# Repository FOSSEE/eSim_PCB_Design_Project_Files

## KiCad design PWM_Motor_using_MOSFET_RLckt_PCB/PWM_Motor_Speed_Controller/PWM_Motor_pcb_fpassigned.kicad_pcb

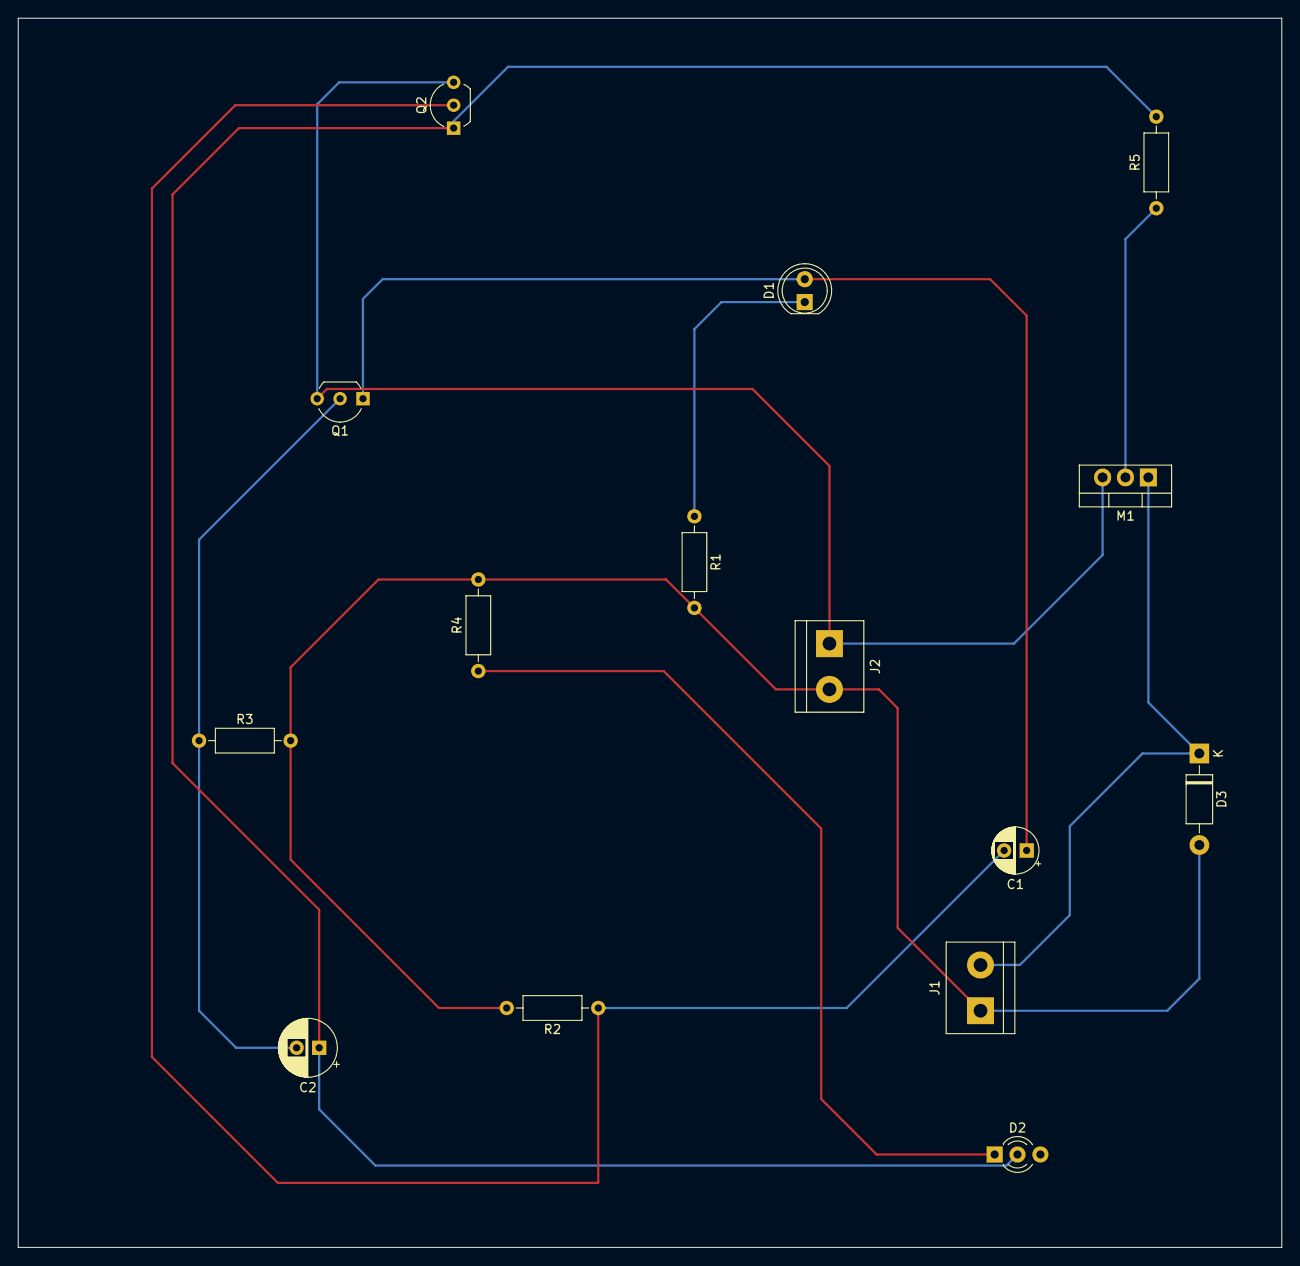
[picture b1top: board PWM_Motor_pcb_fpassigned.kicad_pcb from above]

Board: 2 copper layers, 140.2 x 136.4 mm, 15 parts (0 on the bottom side), 10 nets.

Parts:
C1: 100n; CP_Radial_D5.0mm_P2.50mm
C2: 100n; CP_Radial_D6.3mm_P2.50mm
D1: eSim_LED; LED_D5.0mm
D2: eSim_LED; LED_D3.0mm-3
D3: eSim_Diode; D_DO-41_SOD81_P10.16mm_Horizontal
J1, J2: eSim_2PinConn; TerminalBlock_bornier-2_P5.08mm
M1: eSim_MOS_N; TO-220-3_Vertical
Q1, Q2: eSim_NPN; TO-92_Inline_Wide
R1, R4: 1K; R_Axial_DIN0207_L6.3mm_D2.5mm_P10.16mm_Horizontal
R2: 33k; R_Axial_DIN0207_L6.3mm_D2.5mm_P10.16mm_Horizontal
R3: 100k; R_Axial_DIN0207_L6.3mm_D2.5mm_P10.16mm_Horizontal
R5: 100; R_Axial_DIN0207_L6.3mm_D2.5mm_P10.16mm_Horizontal

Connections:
GND: J2.1, M1.3 (S), Q1.3 (E), Q2.3 (E)
unnamed: C1.1, D1.2 (K), Q1.1 (C)
unnamed: C1.2, Q2.2 (B), R2.1
unnamed: C2.1, D2.2 (K), Q2.1 (C), R5.2
unnamed: C2.2, Q1.2 (B), R3.1
unnamed: D1.1 (A), R1.1
unnamed: D2.1 (A), R4.1
unnamed: D3.1 (A), J1.2, M1.1 (D)
unnamed: D3.2 (K), J1.1, J2.2, R1.2, R2.2, R3.2, R4.2
unnamed: M1.2 (G), R5.1

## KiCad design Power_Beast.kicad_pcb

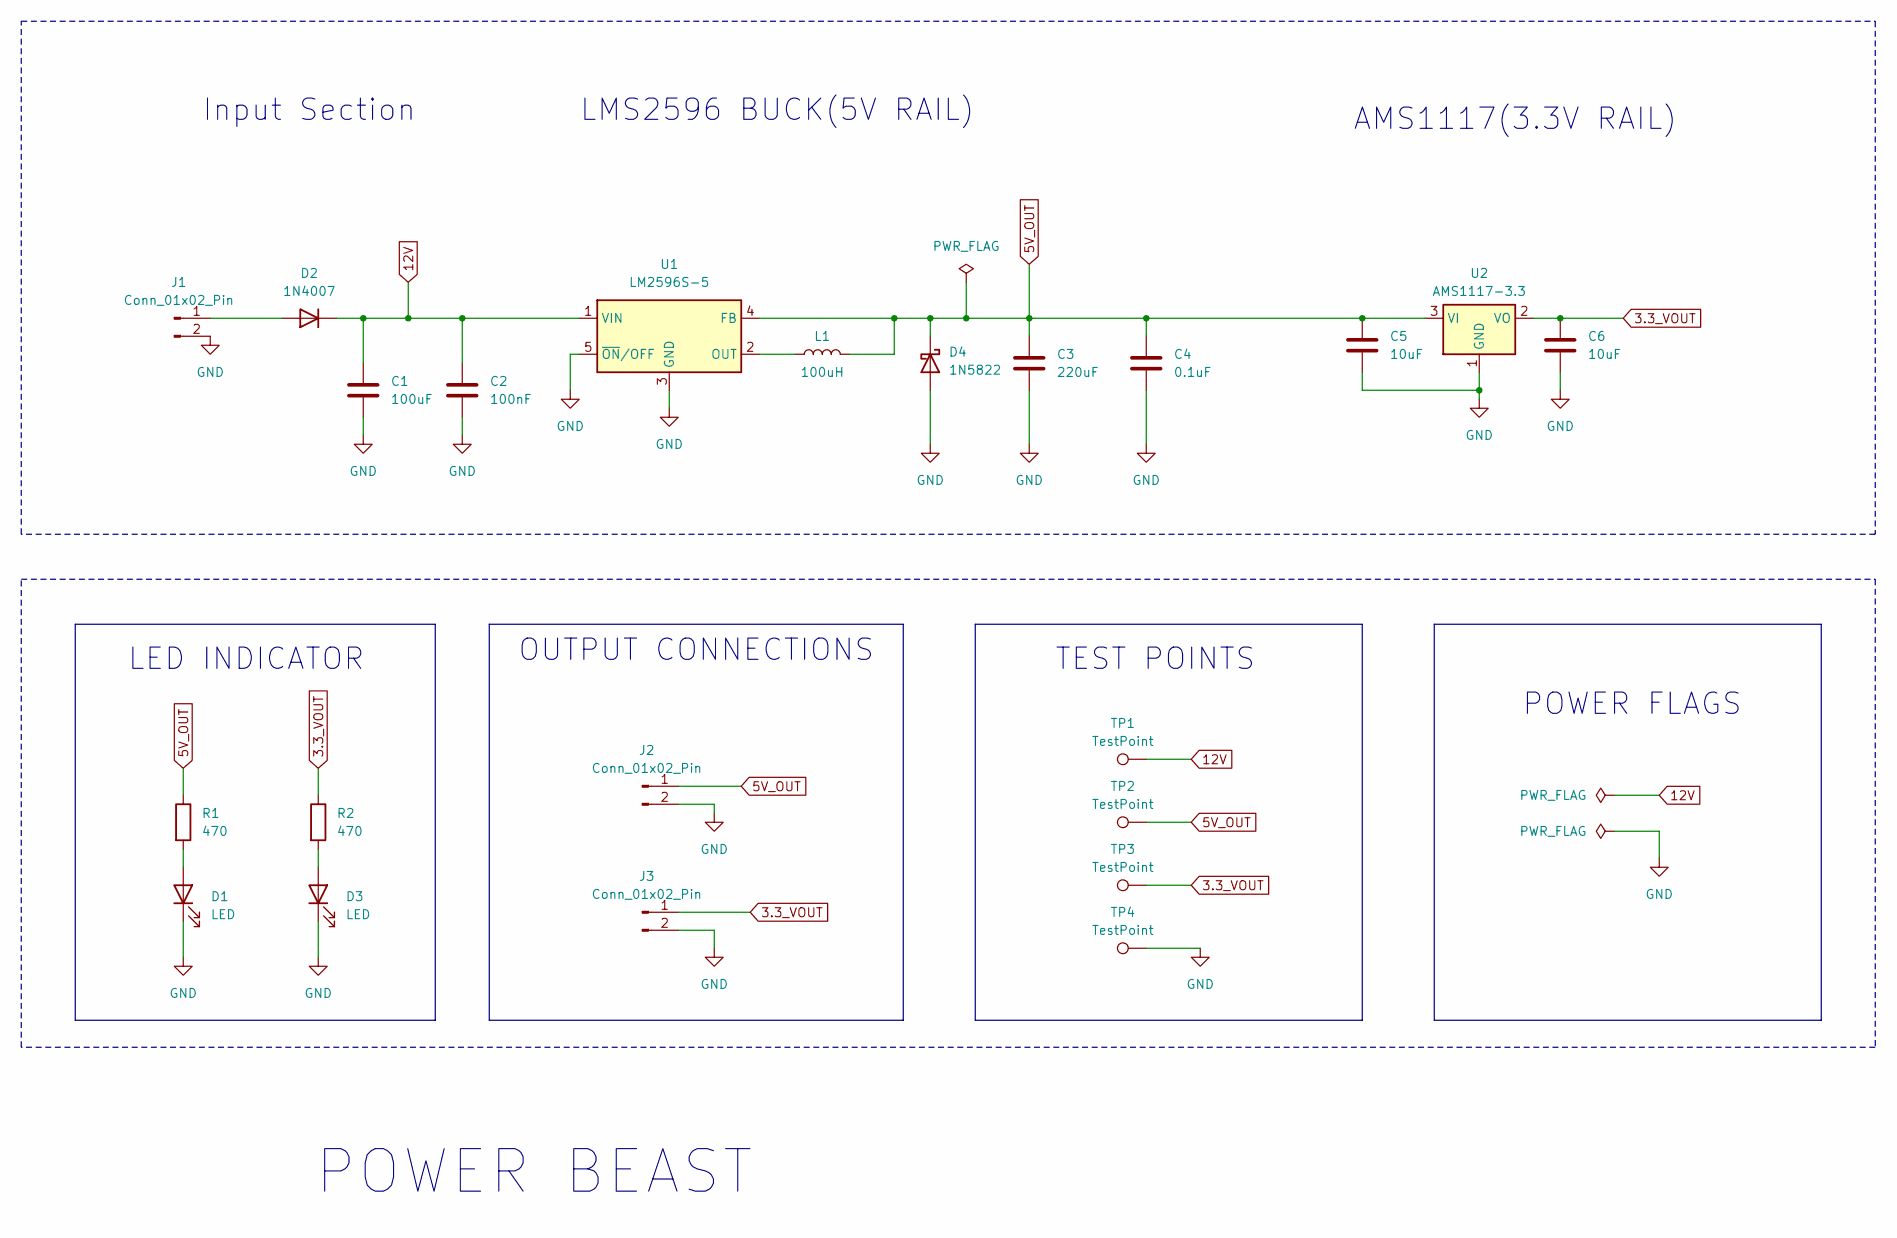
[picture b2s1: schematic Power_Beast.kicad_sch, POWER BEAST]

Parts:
C1: 100uF; CP_Radial_D8.0mm_P3.50mm
C2: 100nF; C_0805_2012Metric
C3: 220uF; CP_Radial_D8.0mm_P3.50mm
C4: 0.1uF; C_0805_2012Metric
C5, C6: 10uF; C_0805_2012Metric
D1, D3: LED; LED_D3.0mm
D2: 1N4007; D_DO-41_SOD81_P10.16mm_Horizontal
D4: 1N5822; D_DO-27_P12.70mm_Horizontal
J1, J2, J3: Conn_01x02_Pin; PinHeader_1x02_P2.54mm_Vertical
L1: 100uH; L_Axial_L9.5mm_D4.0mm_P15.24mm_Horizontal_Fastron_SMCC
R1, R2: 470; R_0805_2012Metric
TP1, TP2, TP3, TP4: TestPoint; TestPoint_Pad_D2.0mm
U1: LM2596S-5; TO-263-5_TabPin6
U2: AMS1117-3.3; SOT-223-3_TabPin2

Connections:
3.3_VOUT: C6.2, J3.1, R2.1, TP3.1 (1_1), U2.2 (VO)
5V_OUT: C3.1, C4.1, C5.1, D4.1 (K), J2.1, L1.2, R1.1, TP2.1 (1_1), U1.4 (FB), U2.3 (VI)
12V: C1.1, C2.1, D2.1 (K), TP1.1 (1_1), U1.1 (VIN)
GND: C1.2, C2.2, C3.2, C4.2, C5.2, C6.1, D1.1 (K), D3.1 (K), D4.2 (A), J1.2, J2.2, J3.2, TP4.1 (1_1), U1.3 (GND), U1.5 (~ON/OFF), U2.1 (GND)
unnamed: D1.2 (A), R1.2
unnamed: D2.2 (A), J1.1
unnamed: D3.2 (A), R2.2
unnamed: L1.1, U1.2 (OUT)

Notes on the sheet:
POWER BEAST
Input Section
LMS2596 BUCK(5V RAIL)
OUTPUT CONNECTIONS
POWER FLAGS
TEST POINTS
LED INDICATOR
AMS1117(3.3V RAIL)

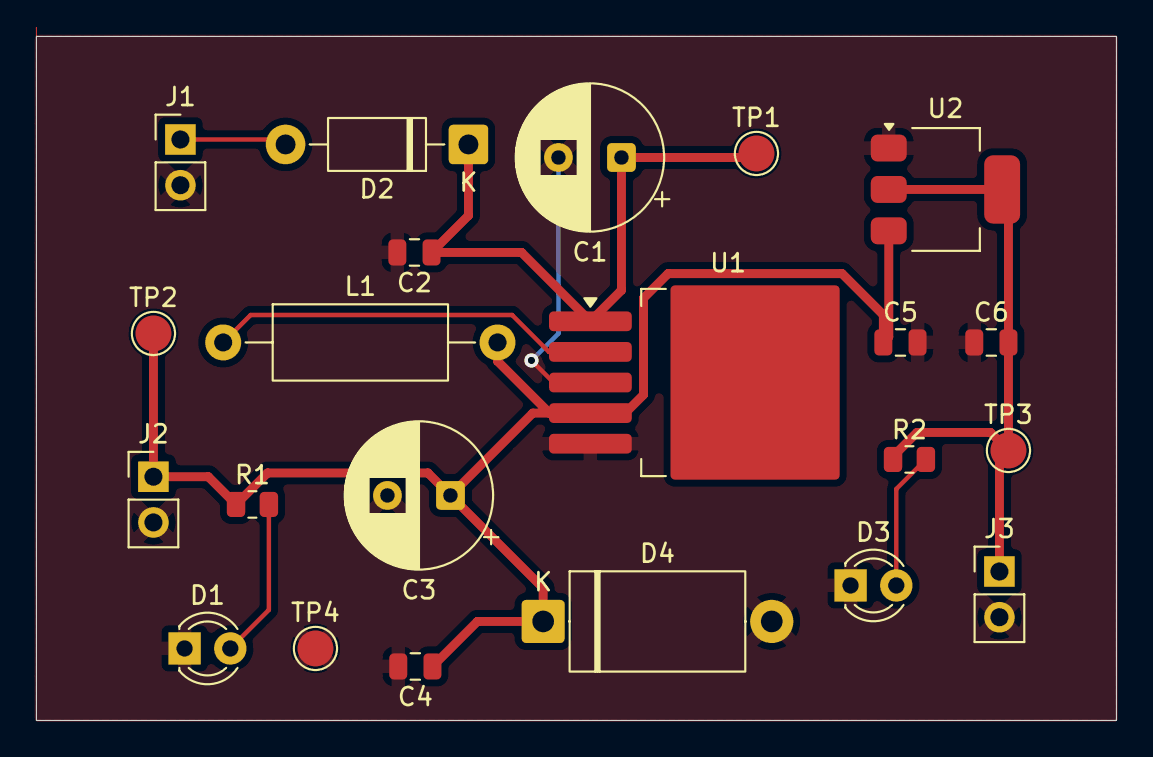
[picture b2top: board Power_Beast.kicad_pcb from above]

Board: 2 copper layers, 60.0 x 38.0 mm, 22 parts (0 on the bottom side), 8 nets.

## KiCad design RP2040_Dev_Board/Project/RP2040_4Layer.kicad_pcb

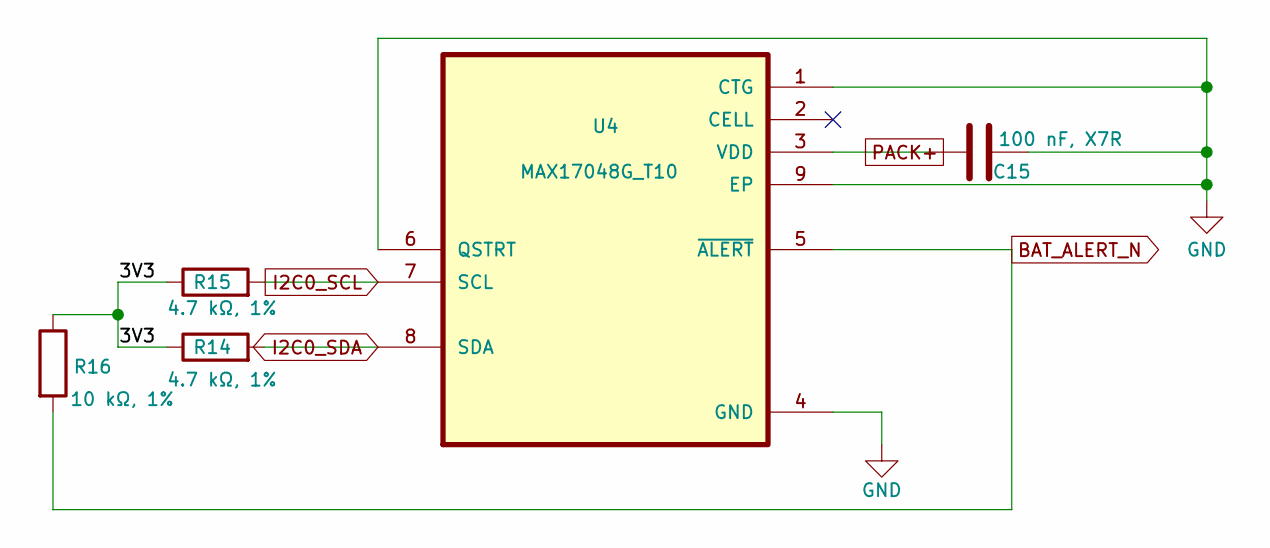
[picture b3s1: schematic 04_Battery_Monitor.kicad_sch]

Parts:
C15: 100 nF, X7R; C_0603_1608Metric
R14, R15: 4.7 kΩ, 1%; R_0603_1608Metric
R16: 10 kΩ, 1%; R_0603_1608Metric
U4: MAX17048G_T10; MAX17048G_T10SON50P200X200X80-9N; MPN MAX17048G+T10

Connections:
/04_Battery_Monitor/3V3: R14.1, R15.1, R16.1
BAT_ALERT_N: R16.2, U4.5 (~ALERT); also elsewhere on the board
GND: C15.2, U4.1 (CTG), U4.4 (GND), U4.6 (QSTRT), U4.9 (EP); also elsewhere on the board
I2C0_SCL: R15.2, U4.7 (SCL); also elsewhere on the board
I2C0_SDA: R14.2, U4.8 (SDA); also elsewhere on the board
PACK+: C15.1, U4.3 (VDD); also elsewhere on the board

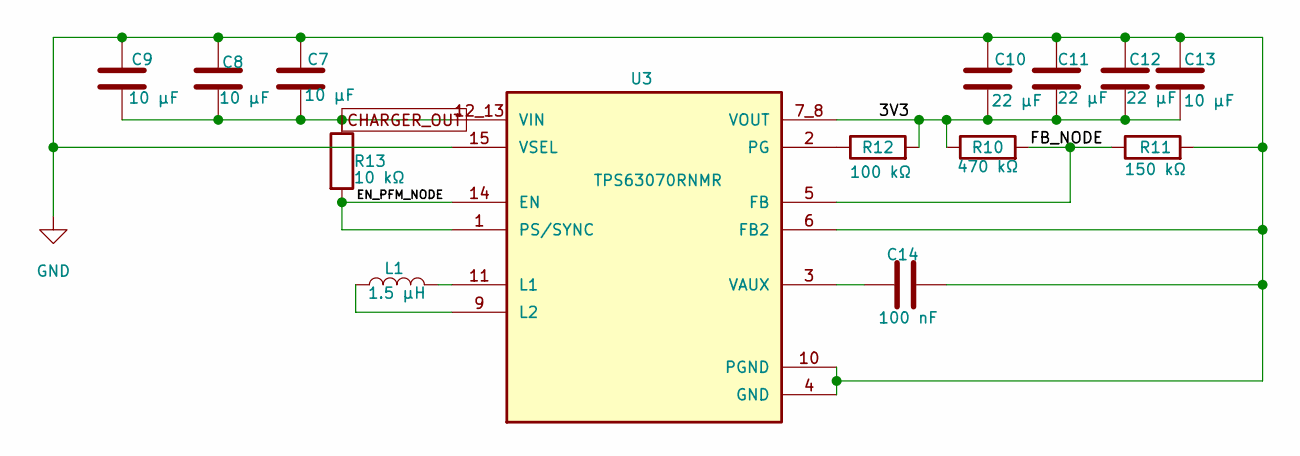
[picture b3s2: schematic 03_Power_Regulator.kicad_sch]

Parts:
C7, C8, C9, C13: 10 µF; C_0805_2012Metric
C10, C11, C12: 22 µF; C_1206_3216Metric
C14: 100 nF; C_0603_1608Metric
L1: 1.5 µH; L_Coilcraft_XxL4020
R10: 470 kΩ; R_0603_1608Metric
R11: 150 kΩ; R_0603_1608Metric
R12: 100 kΩ; R_0603_1608Metric
R13: 10 kΩ; R_0603_1608Metric
U3: TPS63070RNMR; VREG_TPS63070RNMR; MPN TPS63070RNMR

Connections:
/03_Power_Regulator/3V3: C10.2, C11.2, C12.2, C13.2, R10.1, R12.2, U3.7_8 (VOUT)
/03_Power_Regulator/EN_PFM_NODE: R13.2, U3.1 (PS/SYNC), U3.14 (EN)
/03_Power_Regulator/FB_NODE: R10.2, R11.1, U3.5 (FB)
CHARGER_OUT: C7.2, C8.2, C9.2, R13.1, U3.12_13 (VIN); also elsewhere on the board
GND: C7.1, C8.1, C9.1, C10.1, C11.1, C12.1, C13.1, C14.2, R11.2, U3.4 (GND), U3.6 (FB2), U3.10 (PGND), U3.15 (VSEL); also elsewhere on the board
unnamed: L1.2, U3.11 (L1)
unnamed: L1.1, U3.9 (L2)
unnamed: R12.1, U3.2 (PG)
unnamed: C14.1, U3.3 (VAUX)

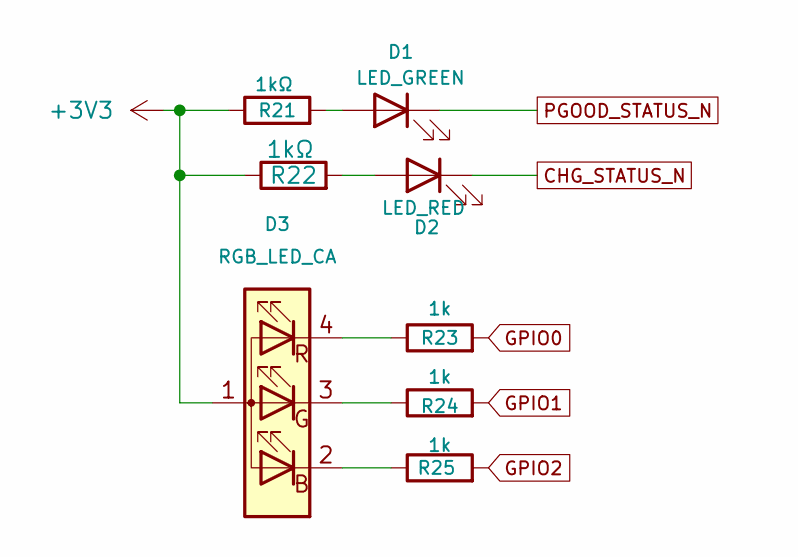
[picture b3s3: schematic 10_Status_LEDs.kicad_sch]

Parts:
D1: LED_GREEN; LED_0603_1608Metric
D2: LED_RED; LED_0603_1608Metric
D3: RGB_LED_CA; LED_Avago_PLCC4_3.2x2.8mm_CW
R21, R22: 1kΩ; R_0603_1608Metric
R23, R24, R25: 1k; R_0603_1608Metric

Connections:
+3V3: D3.1 (A), R21.1, R22.1; also elsewhere on the board
CHG_STATUS_N: D2.1 (K); also elsewhere on the board
GPIO0: R23.2; also elsewhere on the board
GPIO1: R24.2; also elsewhere on the board
GPIO2: R25.2; also elsewhere on the board
unnamed: D1.2 (A), R21.2
unnamed: D2.2 (A), R22.2
unnamed 51: D3.2 (BK), R25.1; also elsewhere on the board
unnamed 52: D3.3 (GK), R24.1; also elsewhere on the board
unnamed 53: D3.4 (RK), R23.1; also elsewhere on the board
PGOOD_STATUS_N: D1.1 (K); also elsewhere on the board

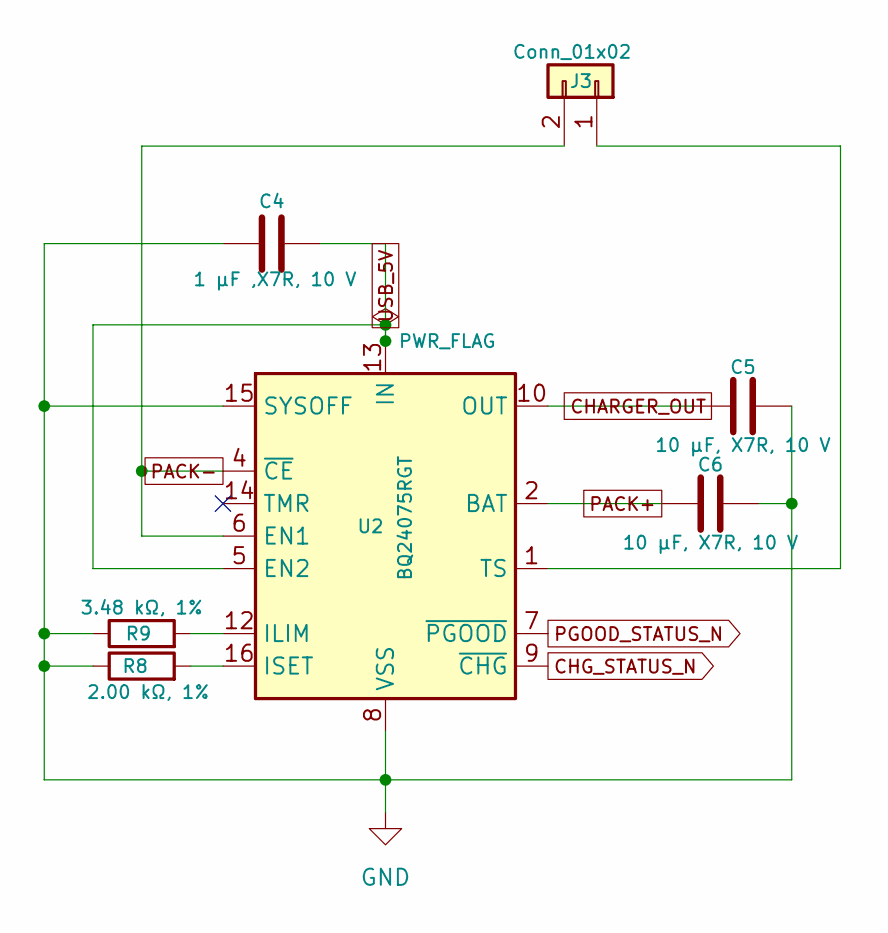
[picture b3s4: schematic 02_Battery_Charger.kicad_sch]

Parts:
C4: 1 µF ,X7R, 10 V; C_0603_1608Metric
C5, C6: 10 µF, X7R, 10 V; C_0805_2012Metric
J3: Conn_01x02; JST_PH_S2B-PH-K_1x02_P2.00mm_Horizontal
R8: 2.00 kΩ, 1%; R_0603_1608Metric
R9: 3.48 kΩ, 1%; R_0603_1608Metric
U2: BQ24075RGT; VQFN-16-1EP_3x3mm_P0.5mm_EP1.6x1.6mm

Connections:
CHARGER_OUT: C5.1, U2.10 (OUT), U2.11 (OUT); also elsewhere on the board
CHG_STATUS_N: U2.9 (~CHG); also elsewhere on the board
GND: C4.1, C5.2, C6.2, R8.1, R9.1, U2.8 (VSS), U2.15 (SYSOFF), U2.17 (VSS); also elsewhere on the board
unnamed 57: J3.1, U2.1 (TS); also elsewhere on the board
unnamed: R9.2, U2.12 (ILIM)
unnamed: R8.2, U2.16 (ISET)
PACK+: C6.1, U2.2 (BAT), U2.3 (BAT); also elsewhere on the board
PACK-: J3.2, U2.4 (~CE), U2.6 (EN1); also elsewhere on the board
PGOOD_STATUS_N: U2.7 (~PGOOD); also elsewhere on the board
USB_5V: C4.2, U2.5 (EN2), U2.13 (IN); also elsewhere on the board

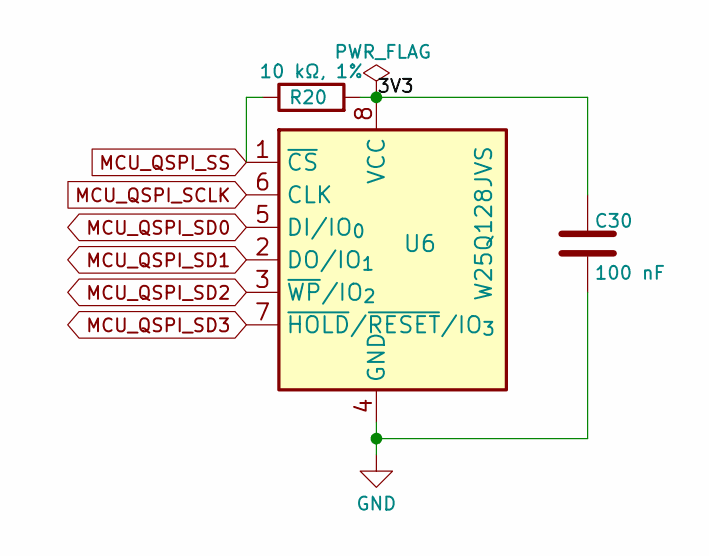
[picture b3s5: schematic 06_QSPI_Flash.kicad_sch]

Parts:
C30: 100 nF; C_0402_1005Metric
R20: 10 kΩ, 1%; R_0402_1005Metric
U6: W25Q128JVS; SOIC-8_5.3x5.3mm_P1.27mm

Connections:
/06_QSPI_Flash/3V3: C30.2, R20.2, U6.8 (VCC)
GND: C30.1, U6.4 (GND); also elsewhere on the board
MCU_QSPI_SCLK: U6.6 (CLK); also elsewhere on the board
MCU_QSPI_SD0: U6.5 (DI/IO_{0}); also elsewhere on the board
MCU_QSPI_SD1: U6.2 (DO/IO_{1}); also elsewhere on the board
MCU_QSPI_SD2: U6.3 (~WP/IO_{2}); also elsewhere on the board
MCU_QSPI_SD3: U6.7 (~HOLD/~RESET/IO_{3}); also elsewhere on the board
MCU_QSPI_SS: R20.1, U6.1 (~CS); also elsewhere on the board

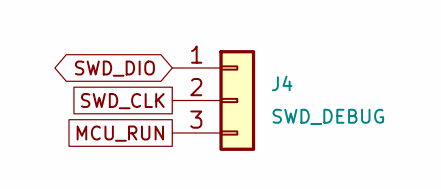
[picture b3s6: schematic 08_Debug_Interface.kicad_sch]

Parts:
J4: SWD_DEBUG; PinHeader_1x03_P2.54mm_Vertical

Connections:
MCU_RUN: J4.3; also elsewhere on the board
SWD_CLK: J4.2; also elsewhere on the board
SWD_DIO: J4.1; also elsewhere on the board

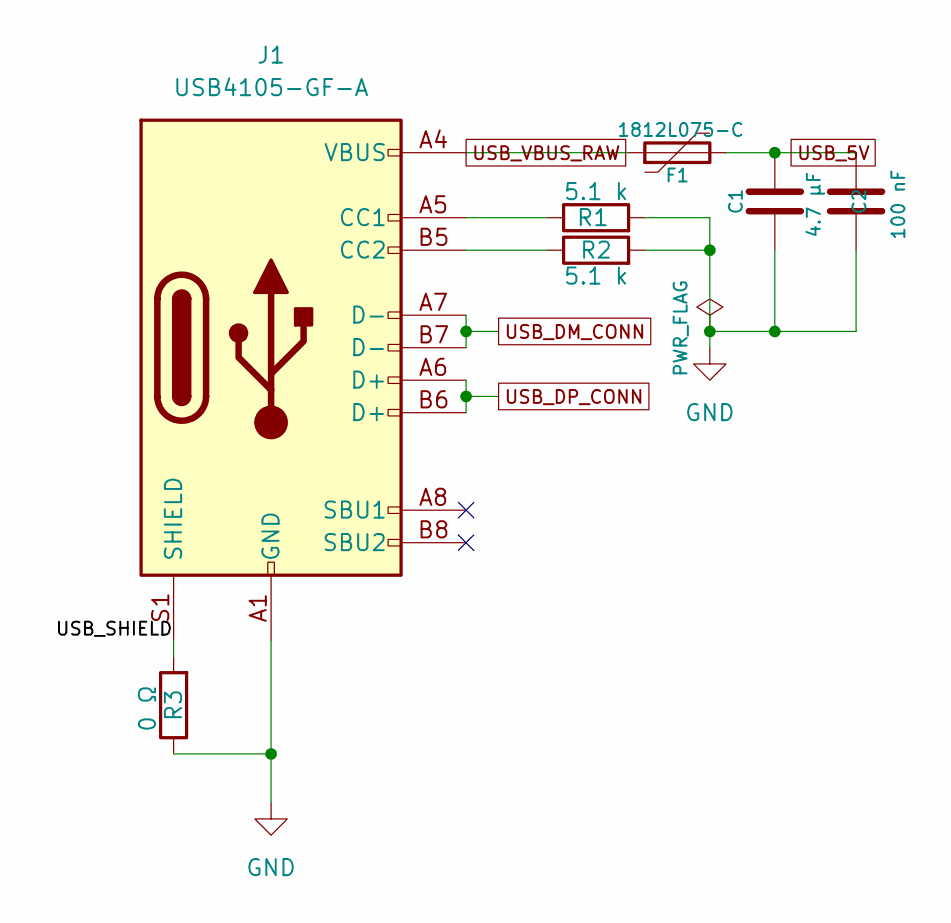
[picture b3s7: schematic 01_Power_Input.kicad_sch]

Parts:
C1: 4.7 µF; C_0603_1608Metric
C2: 100 nF; C_0603_1608Metric
F1: 1812L075-C; Fuse_1812_4532Metric
J1: USB4105-GF-A; USB_C_Receptacle_GCT_USB4105-xx-A_16P_TopMnt_Horizontal
R1, R2: 5.1 k; R_0603_1608Metric
R3: 0 Ω; R_0603_1608Metric

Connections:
/01_Power_Input/USB_SHIELD: J1.S1 (SHIELD), R3.2
GND: C1.2, C2.2, J1.A1 (GND), J1.A12 (GND), J1.B1 (GND), J1.B12 (GND), R1.2, R2.2, R3.1; also elsewhere on the board
unnamed: J1.A5 (CC1), R1.1
unnamed: J1.B5 (CC2), R2.1
USB_5V: C1.1, C2.1, F1.2; also elsewhere on the board
USB_DM_CONN: J1.A7 (D-), J1.B7 (D-); also elsewhere on the board
USB_DP_CONN: J1.A6 (D+), J1.B6 (D+); also elsewhere on the board
USB_VBUS_RAW: F1.1, J1.A4 (VBUS), J1.A9 (VBUS), J1.B4 (VBUS), J1.B9 (VBUS); also elsewhere on the board

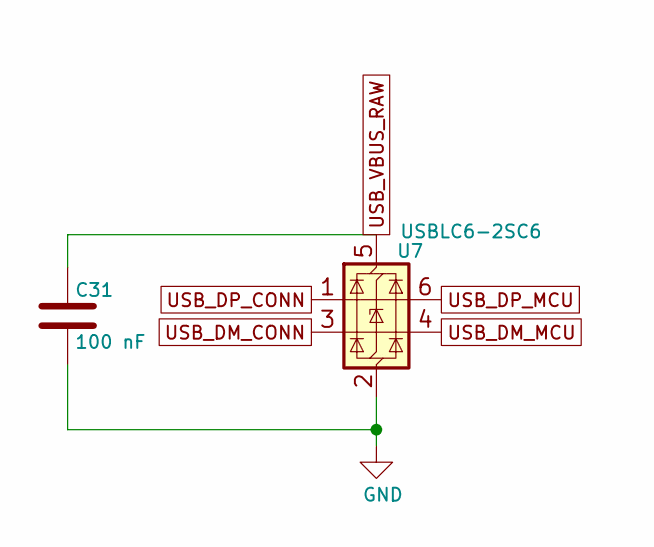
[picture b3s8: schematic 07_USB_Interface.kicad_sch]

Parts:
C31: 100 nF; C_0402_1005Metric
U7: USBLC6-2SC6; SOT-23-6

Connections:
GND: C31.2, U7.2 (GND); also elsewhere on the board
USB_DM_CONN: U7.3 (I/O2); also elsewhere on the board
USB_DM_MCU: U7.4 (I/O2); also elsewhere on the board
USB_DP_CONN: U7.1 (I/O1); also elsewhere on the board
USB_DP_MCU: U7.6 (I/O1); also elsewhere on the board
USB_VBUS_RAW: C31.1, U7.5 (VBUS); also elsewhere on the board

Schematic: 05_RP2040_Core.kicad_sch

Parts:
C16, C17, C18, C19, C20, C21, C22, C23, C24: 100 nF; C_0402_1005Metric
C25, C26: 1 µF; C_0603_1608Metric
C27, C28: 15 pF, 5%, C0G; C_0402_1005Metric
C29: 100 nF, X7R, 0402; C_0402_1005Metric
R17: 1 kΩ, 1%; R_0402_1005Metric
R18, R19: 27 Ω, 1%; R_0402_1005Metric
SW1: RESET; SW_SPST_TL3342
SW2: BOOTSEL; SW_SPST_TL3342
U5: RP2040; QFN-56-1EP_7x7mm_P0.4mm_EP3.2x3.2mm
Y1: Abracon ABM8-272-T3, 12 MHz; Crystal_SMD_3225-4Pin_3.2x2.5mm

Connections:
/05_RP2040_Core/1V1_CORE: C23.1, C24.1, C26.1, U5.23 (DVDD), U5.45 (VREG_VOUT), U5.50 (DVDD)
/05_RP2040_Core/3V3: C16.1, C17.1, C18.1, C19.1, C20.1, C21.1, C22.1, C25.1, C29.1, U5.1 (IOVDD), U5.10 (IOVDD), U5.22 (IOVDD), U5.33 (IOVDD), U5.42 (IOVDD), U5.43 (ADC_AVDD), U5.44 (VREG_IN), U5.48 (USB_VDD), U5.49 (IOVDD)
BAT_ALERT_N: U5.8 (GPIO6); also elsewhere on the board
GND: C16.2, C17.2, C18.2, C19.2, C20.2, C21.2, C22.2, C23.2, C24.2, C25.2, C26.2, C27.1, C28.2, C29.2, SW1.1, SW2.2, U5.19 (TESTEN), U5.57 (GND), Y1.2, Y1.4; also elsewhere on the board
GPIO0: U5.2 (GPIO0); also elsewhere on the board
GPIO1: U5.3 (GPIO1); also elsewhere on the board
GPIO2: U5.4 (GPIO2); also elsewhere on the board
GPIO3: U5.5 (GPIO3); also elsewhere on the board
GPIO7: U5.9 (GPIO7); also elsewhere on the board
GPIO8: U5.11 (GPIO8); also elsewhere on the board
GPIO9: U5.12 (GPIO9); also elsewhere on the board
GPIO10: U5.13 (GPIO10); also elsewhere on the board
GPIO11: U5.14 (GPIO11); also elsewhere on the board
GPIO12: U5.15 (GPIO12); also elsewhere on the board
GPIO13: U5.16 (GPIO13); also elsewhere on the board
GPIO14: U5.17 (GPIO14); also elsewhere on the board
GPIO15: U5.18 (GPIO15); also elsewhere on the board
GPIO18: U5.29 (GPIO18); also elsewhere on the board
GPIO19: U5.30 (GPIO19); also elsewhere on the board
GPIO20: U5.31 (GPIO20); also elsewhere on the board
GPIO21: U5.32 (GPIO21); also elsewhere on the board
GPIO22: U5.34 (GPIO22); also elsewhere on the board
GPIO23: U5.35 (GPIO23); also elsewhere on the board
GPIO24: U5.36 (GPIO24); also elsewhere on the board
GPIO25: U5.37 (GPIO25); also elsewhere on the board
GPIO26_ADC0: U5.38 (GPIO26_ADC0); also elsewhere on the board
GPIO27_ADC1: U5.39 (GPIO27_ADC1); also elsewhere on the board
GPIO28_ADC2: U5.40 (GPIO28_ADC2); also elsewhere on the board
GPIO29_ADC3: U5.41 (GPIO29_ADC3); also elsewhere on the board
I2C0_SCL: U5.7 (GPIO5); also elsewhere on the board
I2C0_SDA: U5.6 (GPIO4); also elsewhere on the board
MCU_QSPI_SCLK: U5.52 (QSPI_SCLK); also elsewhere on the board
MCU_QSPI_SD0: U5.53 (QSPI_SD0); also elsewhere on the board
MCU_QSPI_SD1: U5.55 (QSPI_SD1); also elsewhere on the board
MCU_QSPI_SD2: U5.54 (QSPI_SD2); also elsewhere on the board
MCU_QSPI_SD3: U5.51 (QSPI_SD3); also elsewhere on the board
MCU_QSPI_SS: SW2.1, U5.56 (QSPI_SS); also elsewhere on the board
MCU_RUN: SW1.2, U5.26 (RUN); also elsewhere on the board
unnamed: C28.1, R17.1, Y1.3
unnamed: R19.2, U5.46 (USB_DM)
unnamed: R18.2, U5.47 (USB_DP)
unnamed: C27.2, U5.20 (XIN), Y1.1
unnamed: R17.2, U5.21 (XOUT)
SWD_CLK: U5.24 (SWCLK); also elsewhere on the board
SWD_DIO: U5.25 (SWD); also elsewhere on the board
UART0_RX: U5.28 (GPIO17); also elsewhere on the board
UART0_TX: U5.27 (GPIO16); also elsewhere on the board
USB_DM_MCU: R19.1; also elsewhere on the board
USB_DP_MCU: R18.1; also elsewhere on the board

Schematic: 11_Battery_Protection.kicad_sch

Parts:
C3: 100 nF, X7R; C_0603_1608Metric
F2: 0440002.WRA (2A); Fuse_1206_3216Metric
J2: BATTERY(B2B-PH-K-S); JST_PH_S2B-PH-K_1x02_P2.00mm_Horizontal
Q1, Q2: CSD17308Q3
R4: 2.2 kΩ; R_0603_1608Metric
R5: 330 Ω; R_0603_1608Metric
R6, R7: 5.1 MΩ; R_0603_1608Metric
U1: BQ29700DSER; WSON-6_1.5x1.5mm_P0.5mm

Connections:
/11_Battery_Protection/CELL_NEG: C3.2, J2.2, Q2.3 (S), R7.1, U1.4 (VSS); also elsewhere on the board
unnamed 56: F2.2, J2.1; also elsewhere on the board
unnamed: Q1.2 (D), Q2.2 (D)
unnamed: Q1.1 (G), R6.2, U1.2 (Cout)
unnamed: Q2.1 (G), R7.2, U1.3 (Dout)
unnamed: C3.1, R5.2, U1.5 (BAT)
unnamed: R4.2, U1.6 (V-)
PACK+: F2.1, R5.1; also elsewhere on the board
PACK-: Q1.3 (S), R4.1, R6.1; also elsewhere on the board

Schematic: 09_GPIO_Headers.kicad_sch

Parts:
J5: GPIO_HEADER_A; PinHeader_1x20_P2.54mm_Vertical
J6: GPIO_HEADER_B; PinHeader_1x14_P2.54mm_Vertical
J7: MCU_RESET; PinHeader_1x02_P2.54mm_Vertical

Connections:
+3V3: J5.1, J6.1; also elsewhere on the board
BAT_ALERT_N: J5.9; also elsewhere on the board
GND: J5.2, J6.2, J7.2; also elsewhere on the board
GPIO0: J5.3; also elsewhere on the board
GPIO1: J5.4; also elsewhere on the board
GPIO2: J5.5; also elsewhere on the board
GPIO3: J5.6; also elsewhere on the board
GPIO7: J5.10; also elsewhere on the board
GPIO8: J5.11; also elsewhere on the board
GPIO9: J5.12; also elsewhere on the board
GPIO10: J5.13; also elsewhere on the board
GPIO11: J5.14; also elsewhere on the board
GPIO12: J5.15; also elsewhere on the board
GPIO13: J5.16; also elsewhere on the board
GPIO14: J5.17; also elsewhere on the board
GPIO15: J5.18; also elsewhere on the board
GPIO18: J6.3; also elsewhere on the board
GPIO19: J6.4; also elsewhere on the board
GPIO20: J6.5; also elsewhere on the board
GPIO21: J6.6; also elsewhere on the board
GPIO22: J6.7; also elsewhere on the board
GPIO23: J6.8; also elsewhere on the board
GPIO24: J6.9; also elsewhere on the board
GPIO25: J6.10; also elsewhere on the board
GPIO26_ADC0: J6.11; also elsewhere on the board
GPIO27_ADC1: J6.12; also elsewhere on the board
GPIO28_ADC2: J6.13; also elsewhere on the board
GPIO29_ADC3: J6.14; also elsewhere on the board
I2C0_SCL: J5.8; also elsewhere on the board
I2C0_SDA: J5.7; also elsewhere on the board
MCU_RUN: J7.1; also elsewhere on the board
UART0_RX: J5.20; also elsewhere on the board
UART0_TX: J5.19; also elsewhere on the board

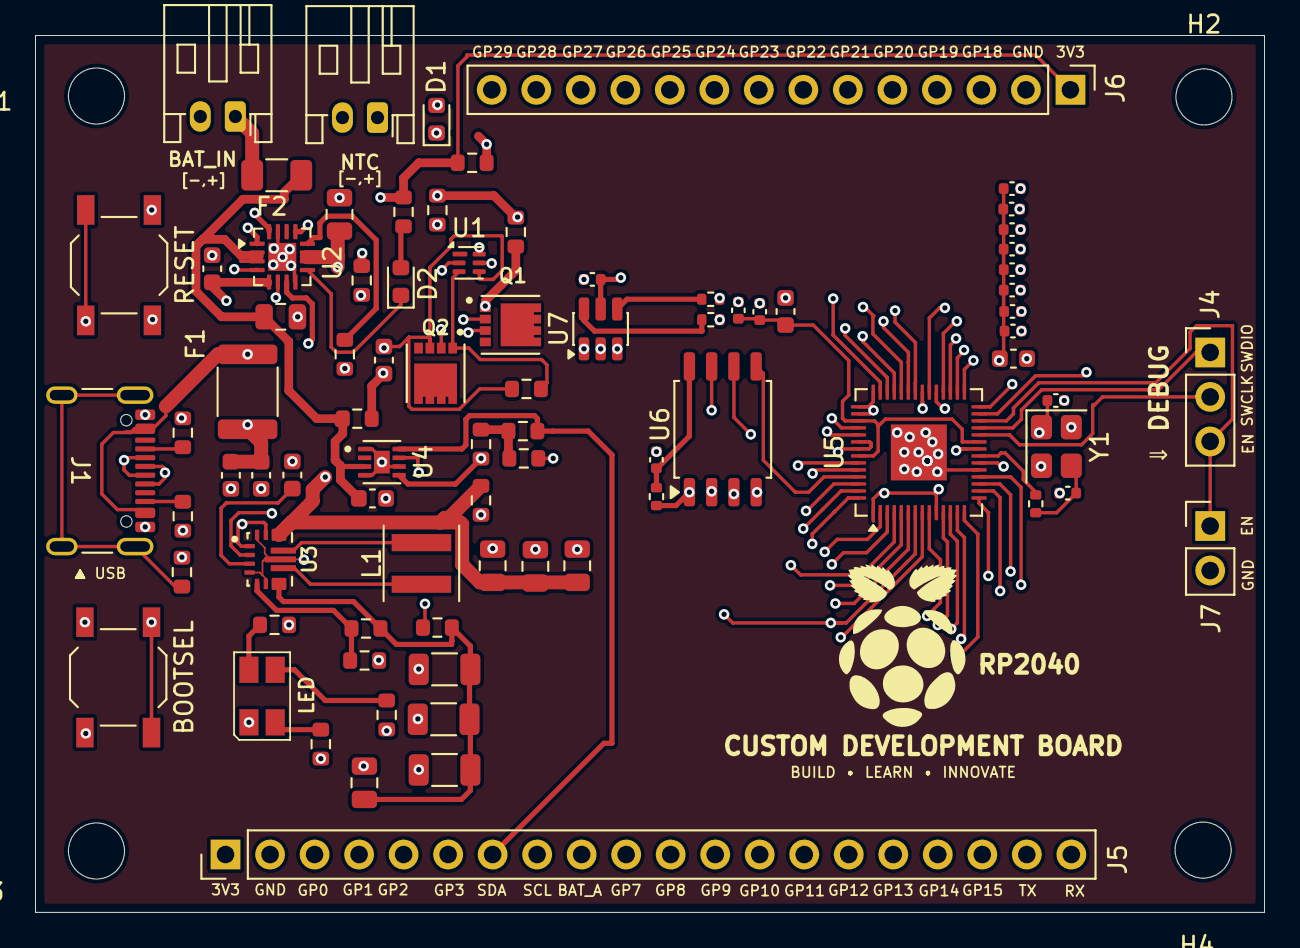
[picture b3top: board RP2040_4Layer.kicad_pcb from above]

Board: 4 copper layers, 70.1 x 50.0 mm, 85 parts (0 on the bottom side), 86 nets.

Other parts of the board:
BAT_IN: BATTERY(B2B-PH-K-S); JST_PH_S2B-PH-K_1x02_P2.00mm_Horizontal
BOOTSEL: BOOTSEL; SW_SPST_TL3342
H1, H2, H3, H4: MountingHole_3.2mm_M3
LED: RGB_LED_CA; LED_Avago_PLCC4_3.2x2.8mm_CW
NTC: Conn_01x02; JST_PH_S2B-PH-K_1x02_P2.00mm_Horizontal
RESET: RESET; SW_SPST_TL3342

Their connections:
+3V3: LED.1 (A); also elsewhere on the board
/11_Battery_Protection/CELL_NEG: BAT_IN.2; also elsewhere on the board
GND: BOOTSEL.2, RESET.1; also elsewhere on the board
MCU_QSPI_SS: BOOTSEL.1; also elsewhere on the board
MCU_RUN: RESET.2; also elsewhere on the board
unnamed 51: LED.2 (BK); also elsewhere on the board
unnamed 52: LED.3 (GK); also elsewhere on the board
unnamed 53: LED.4 (RK); also elsewhere on the board
unnamed 56: BAT_IN.1; also elsewhere on the board
unnamed 57: NTC.1; also elsewhere on the board
PACK-: NTC.2; also elsewhere on the board

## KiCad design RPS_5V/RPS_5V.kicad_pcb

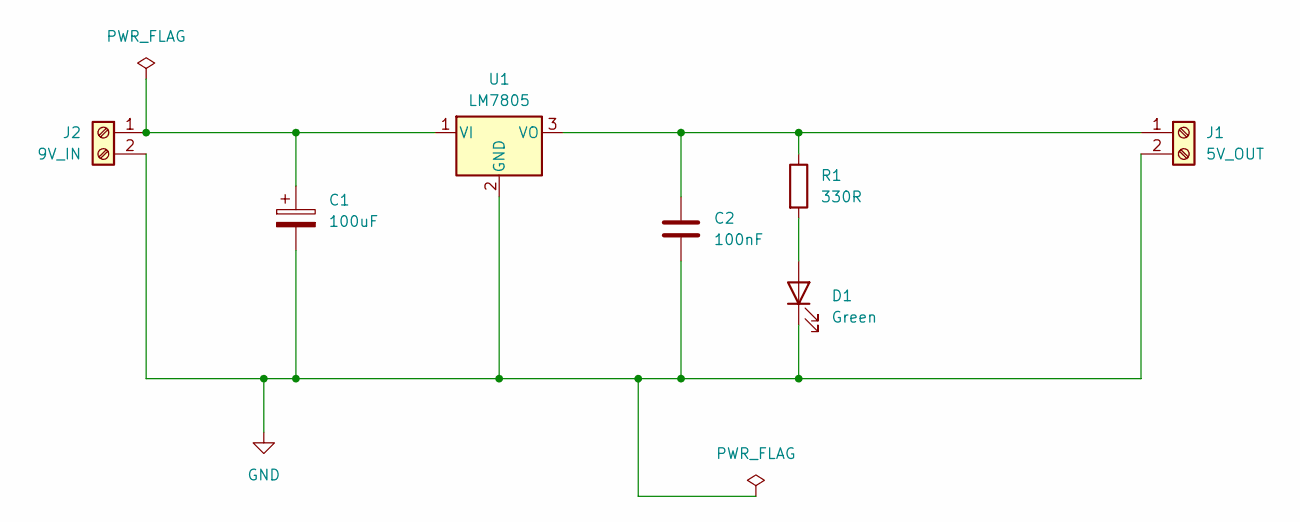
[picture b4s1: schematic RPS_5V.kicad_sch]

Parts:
C1: 100uF; CP_Radial_D8.0mm_P3.50mm
C2: 100nF; C_Disc_D5.0mm_W2.5mm_P5.00mm
D1: Green; LED_D5.0mm
J1: 5V_OUT; TerminalBlock_bornier-2_P5.08mm
J2: 9V_IN; TerminalBlock_Phoenix_MKDS-1,5-2-5.08_1x02_P5.08mm_Horizont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
R1: 330R; R_Axial_DIN0207_L6.3mm_D2.5mm_P10.16mm_Horizontal
U1: LM7805; TO-220-3_Vertical

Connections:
GND: C1.2, C2.2, D1.1 (K), J1.2, J2.2, U1.2 (GND)
unnamed: D1.2 (A), R1.2
unnamed: C2.1, J1.1, R1.1, U1.3 (VO)
unnamed: C1.1, J2.1, U1.1 (VI)

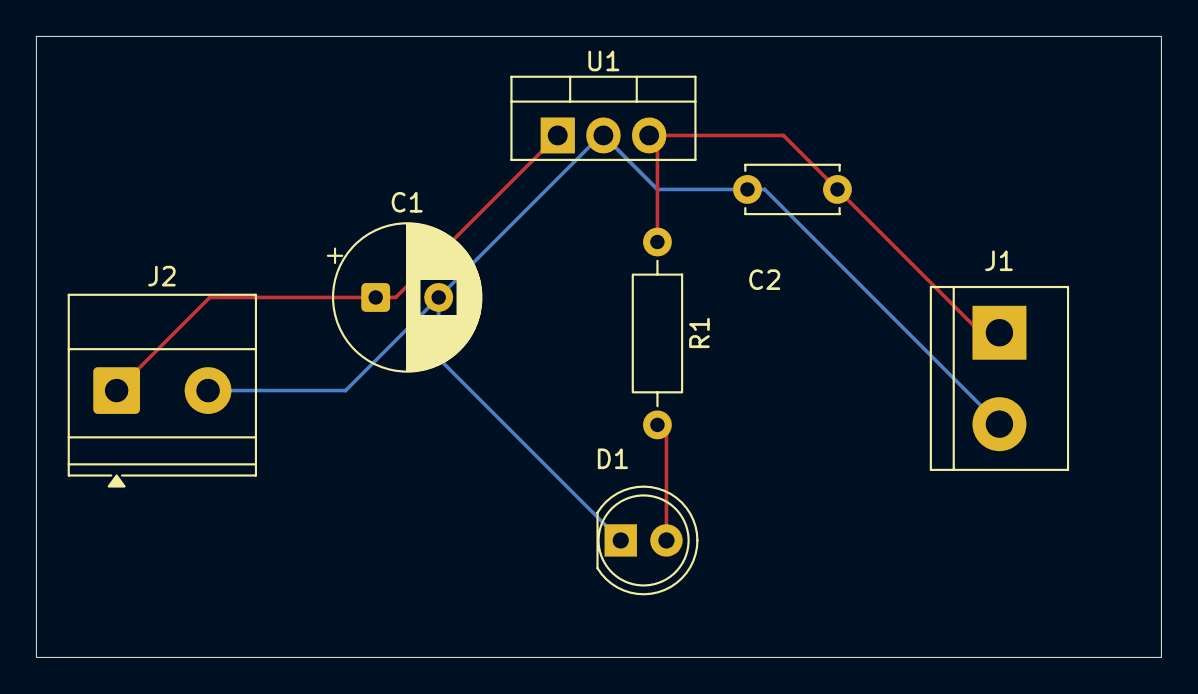
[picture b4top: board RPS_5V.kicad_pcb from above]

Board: 2 copper layers, 62.5 x 34.5 mm, 7 parts (0 on the bottom side), 4 nets.
